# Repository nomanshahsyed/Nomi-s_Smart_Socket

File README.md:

# Nomi-s_Smart_Socket
WiFi Controlled Smart Socket.

The socket was bought from clas ohlson. The socket is 2x2 Euro socket. The PCB has four relay's along with 4 LED's. The PCB fits inside the socket housing and there is a 3d printed casing for the socket. Step file can be found in the files. 3d Casing was designed by Harri Kuittinen. https://www.linkedin.com/in/harri-kuittinen-link/

Eagle schematics and Layout is attached along with the arduino code. WiFi uC is ESP8266. This version 1 is controlled with Thinger.io which is a cloud platform. You can have 2 devices for free int he platform so just sign up and make a device and copy the device information into the program and upload.

I will also make mobile application for this project and upload here.

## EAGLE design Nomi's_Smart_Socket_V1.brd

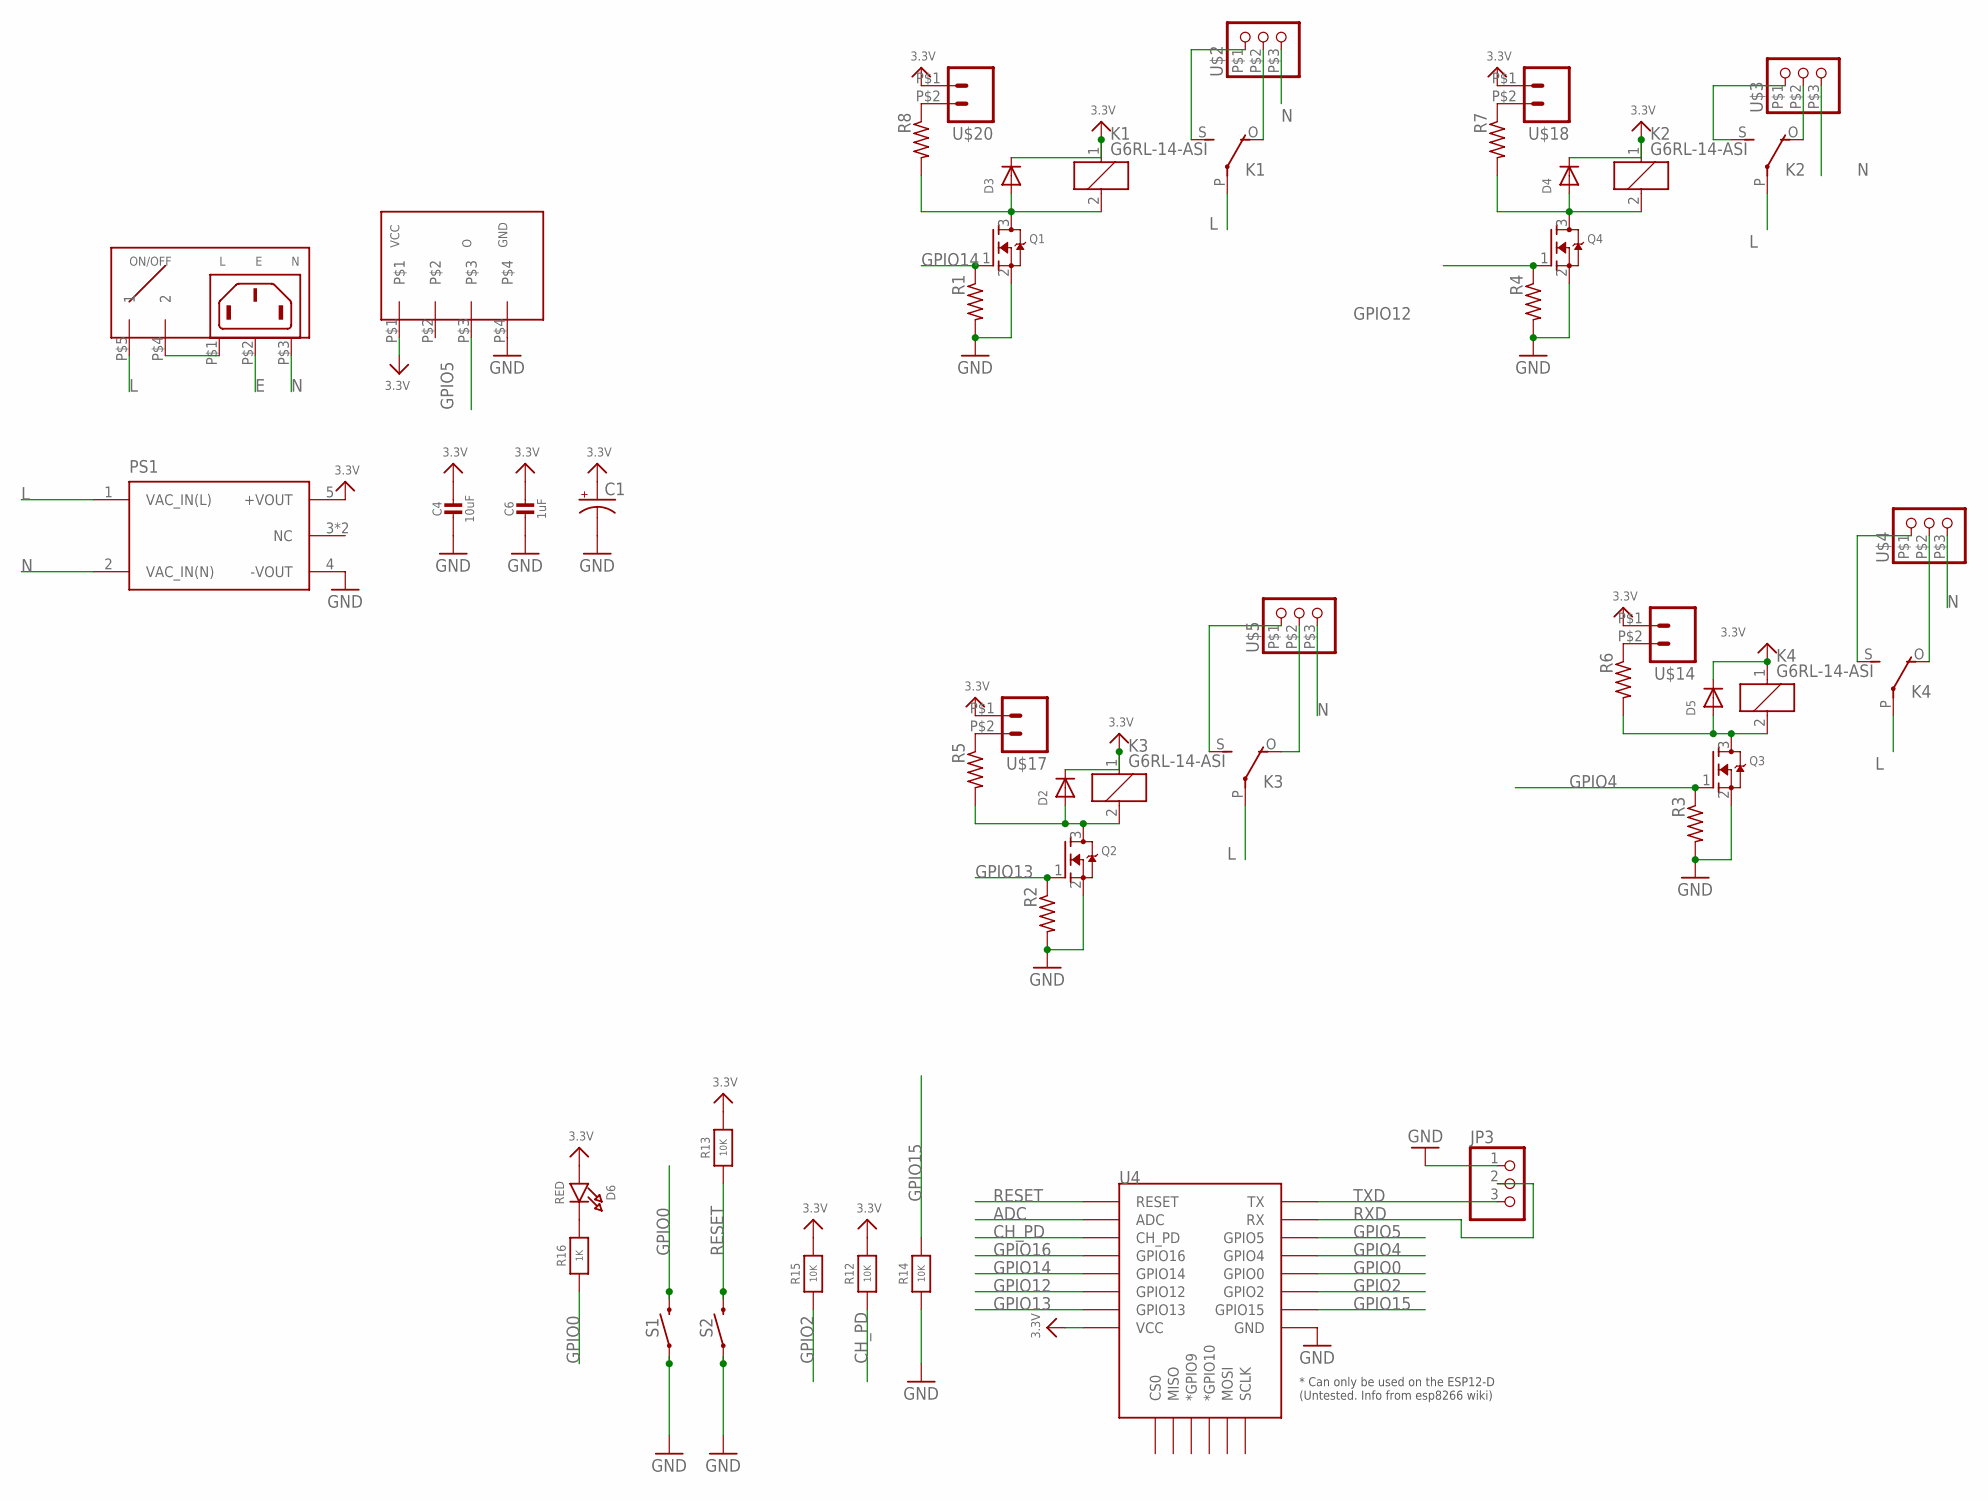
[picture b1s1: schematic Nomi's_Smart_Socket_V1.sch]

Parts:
C1: CPOL-USE5-10.5; E5-10,5
C4: 10uF; _0805
C6: 1uF; _0603
D2, D3, D4, D5: DIODE_SOD-123FL; SOD-123FL
D6: RED; CHIPLED_0805_NOOUTLINE
JP3: PINHD-1X3; 1X03
K1, K2, K3, K4: G6RL-14-ASI; G6RW
PS1: RAC04-3.3SGBRAC04-3.3SGB-3D; DIP1778W80P508L3670H1500Q6B
Q1, Q2, Q3, Q4: MOSFET-NREFLOW; SOT23
R1, R2, R3, R4: 10k; R0603
R5, R6, R7, R8: 22; R0603
R12, R13, R14, R15: 10K; _0603
R16: 1K; _0603
S1, S2: MOMENTARY-SWITCH-SPST-SMD-4.6X2.8MM; TACTILE_SWITCH_SMD_4.6X2.8MM
U4: ESP12FSMD; ESP12F
U$1: AC-CONN-WITH-SWITCH
U$2, U$3, U$4, U$5: TERM-BLOCK-3POS-5MM5MM; TERM-BLOCK-3POS-5MM
U$13: DHT22
U$14, U$17, U$18, U$20: TERMINAL-BLOCK-2POS-2.54MM

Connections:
3.3V: C1.+, C4.1, C6.1, D2.C, D3.C, D4.C, D5.C, D6.A, K1.1, K2.1, K3.1, K4.1, PS1.5 (+VOUT), R12.2, R13.2, R15.2, U4.3.3V (VCC), U$13.P$1, U$14.P$1 (1), U$17.P$1 (1), U$18.P$1 (1), U$20.P$1 (1)
ADC: U4.ADC
CH_PD: R12.1, U4.EN (CH_PD)
E: U$1.P$2 (EARTH)
GND: C1.-, C4.2, C6.2, JP3.1, PS1.4 (-VOUT), Q1.2 (S), Q2.2 (S), Q3.2 (S), Q4.2 (S), R1.2, R2.2, R3.2, R4.2, R14.1, S1.1, S1.2 (1), S2.1, S2.2 (1), U4.GND, U$13.P$4
GPIO0: R16.1, S1.3 (2), S1.4 (2), U4.GPIO0
GPIO2: R15.1, U4.GPIO2
GPIO4: Q3.1 (G), R3.1, U4.GPIO4
GPIO5: U4.GPIO5, U$13.P$3
GPIO12: Q4.1 (G), R4.1, U4.GPIO12
GPIO13: Q2.1 (G), R2.1, U4.GPIO13
GPIO14: Q1.1 (G), R1.1, U4.GPIO14
GPIO15: R14.2, U4.GPIO15
GPIO16: U4.GPIO16
L: K1.P, K2.P, K3.P, K4.P, PS1.1 (VAC_IN(L)), U$1.P$5 (1)
N: PS1.2 (VAC_IN(N)), U$1.P$3 (N), U$2.P$3 (3), U$3.P$3 (3), U$4.P$3 (3), U$5.P$3 (3)
unnamed: U$1.P$1 (L), U$1.P$4 (2)
unnamed: D5.A, K4.2, Q3.3 (D), R6.2
unnamed: D2.A, K3.2, Q2.3 (D), R5.2
unnamed: D3.A, K1.2, Q1.3 (D), R8.2
unnamed: D6.C, R16.2
unnamed: D4.A, K2.2, Q4.3 (D), R7.2
unnamed: K4.O, U$4.P$2 (2)
unnamed: K2.O, U$3.P$2 (2)
unnamed: R5.1, U$17.P$2 (2)
unnamed: R6.1, U$14.P$2 (2)
unnamed: R7.1, U$18.P$2 (2)
unnamed: R8.1, U$20.P$2 (2)
unnamed: K4.S, U$4.P$1 (1)
unnamed: K3.O, U$5.P$2 (2)
unnamed: K1.S, U$2.P$1 (1)
unnamed: K1.O, U$2.P$2 (2)
unnamed: K2.S, U$3.P$1 (1)
unnamed: K3.S, U$5.P$1 (1)
RESET: R13.1, S2.3 (2), S2.4 (2), U4.RST (RESET)
RXD: JP3.2, U4.RXD (RX)
TXD: JP3.3, U4.TXD (TX)

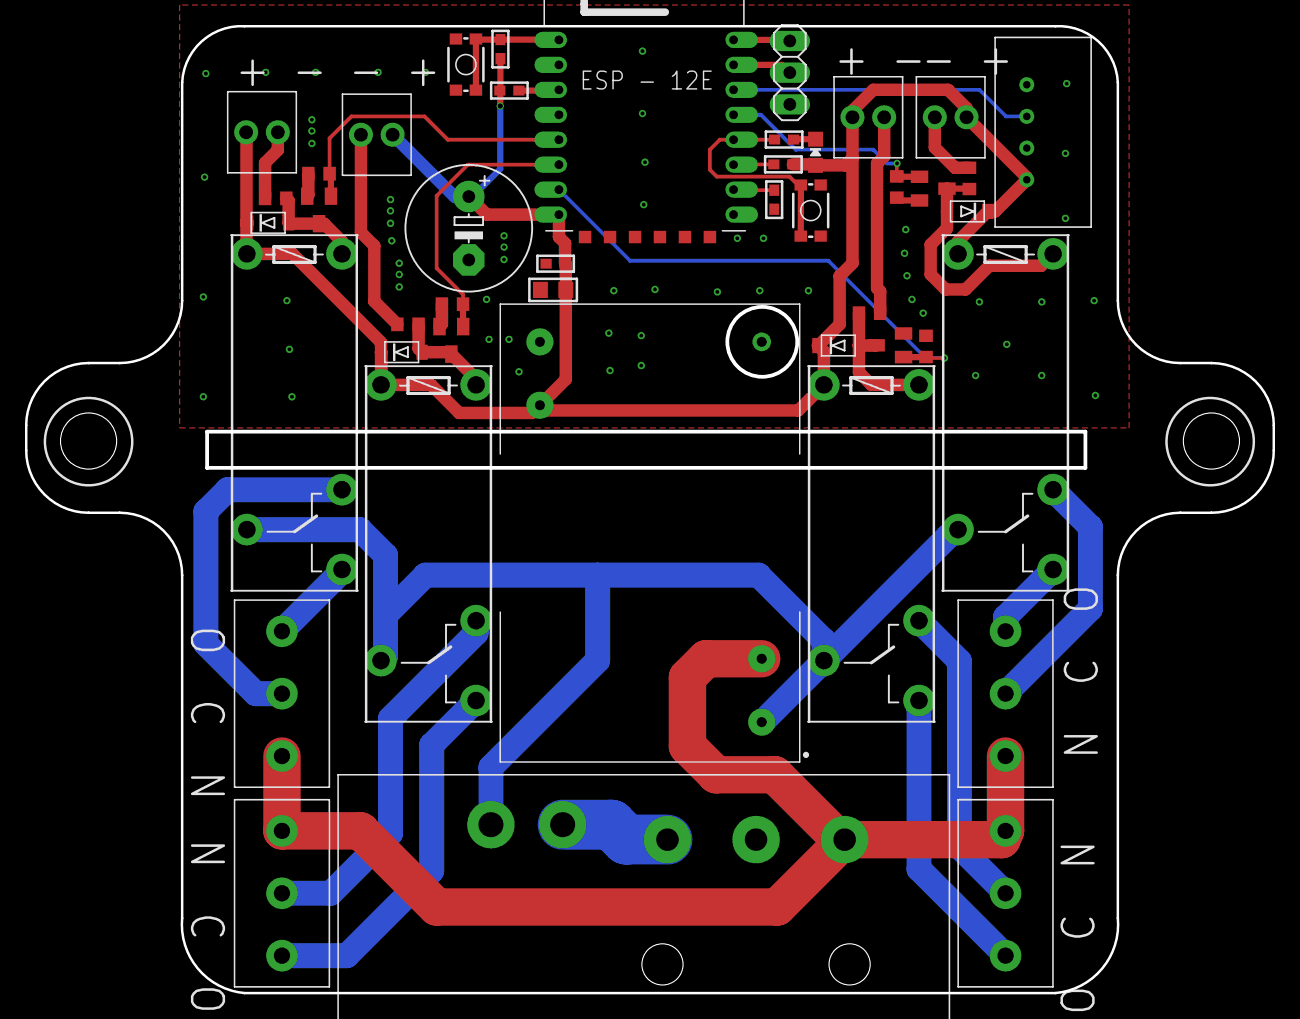
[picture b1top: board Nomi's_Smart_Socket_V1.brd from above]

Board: 2 copper layers, 99.9 x 77.4 mm, 44 parts (0 on the bottom side), 34 nets.

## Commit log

2019-10-28 Version 1
    WiFi Controlled Smart Socket.
    The socket was bought from clas ohlson. The socket is 2x2 Euro socket. The PCB has four relay's along with 4 LED's. The PCB fits inside the socket housing and there is a 3d printed casing for the soc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
    Eagle schematics and Layout is attached along with the arduino code. WiFi uC is ESP8266. This version 1 is controlled with Thinger.io which is a cloud platform. You can have 2 devices for free int he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
2019-10-28 Pictures for assembly.
2021-04-27 Smart Socket with WPS connection with the router.
    Press the WPS button on router when the LED1 turns on.

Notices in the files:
parts and their libraries:
microbuilder: This work is placed in the public domain, and may be freely used for commercial and non-commercial work with the following conditions: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
SparkFun-Switches: Licensing: Creative Commons ShareAlike 4.0 International - https://creativecommons.org/licenses/by-sa/4.0
